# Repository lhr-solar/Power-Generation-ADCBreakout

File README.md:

# PowerGen-ADCBreakout  

Mouser Cart: https://www.mouser.com/Tools/Project/Share?AccessID=0415efee36

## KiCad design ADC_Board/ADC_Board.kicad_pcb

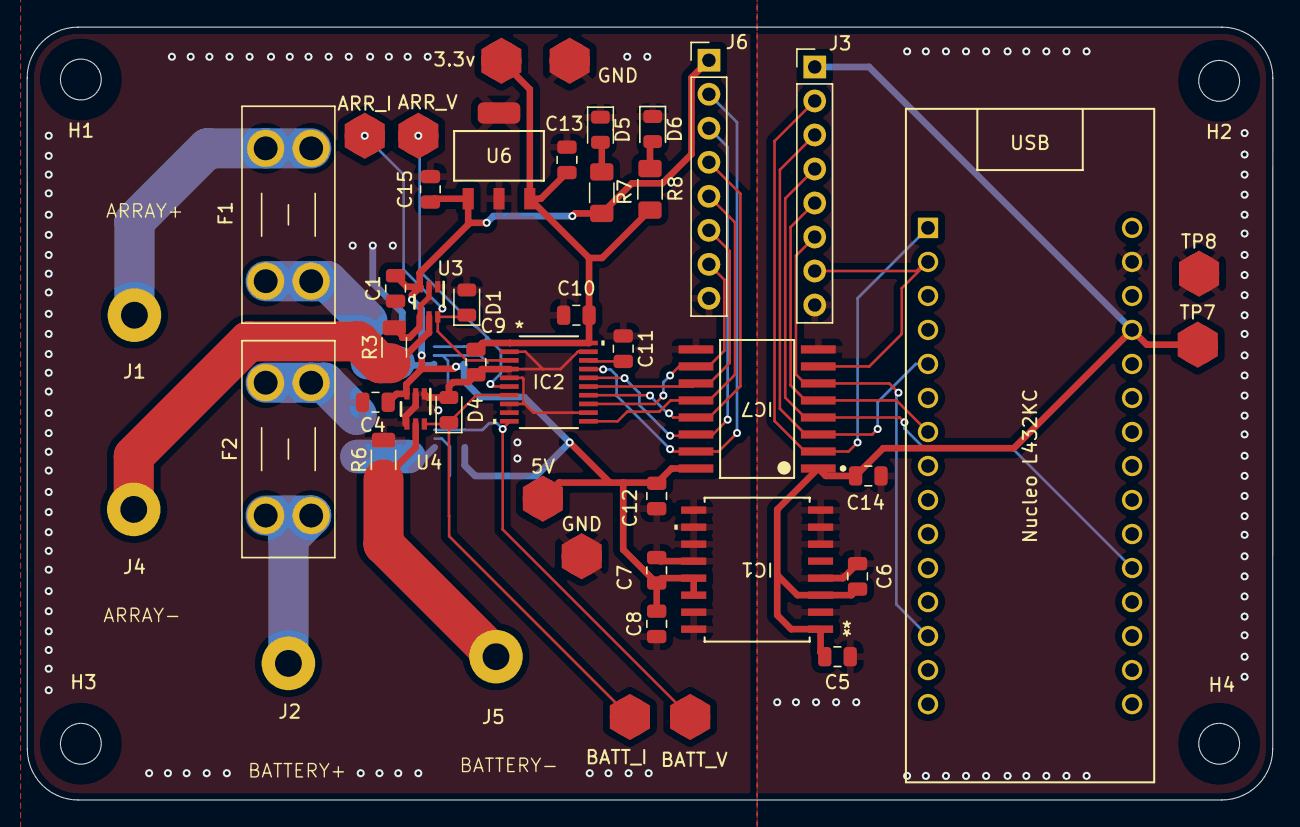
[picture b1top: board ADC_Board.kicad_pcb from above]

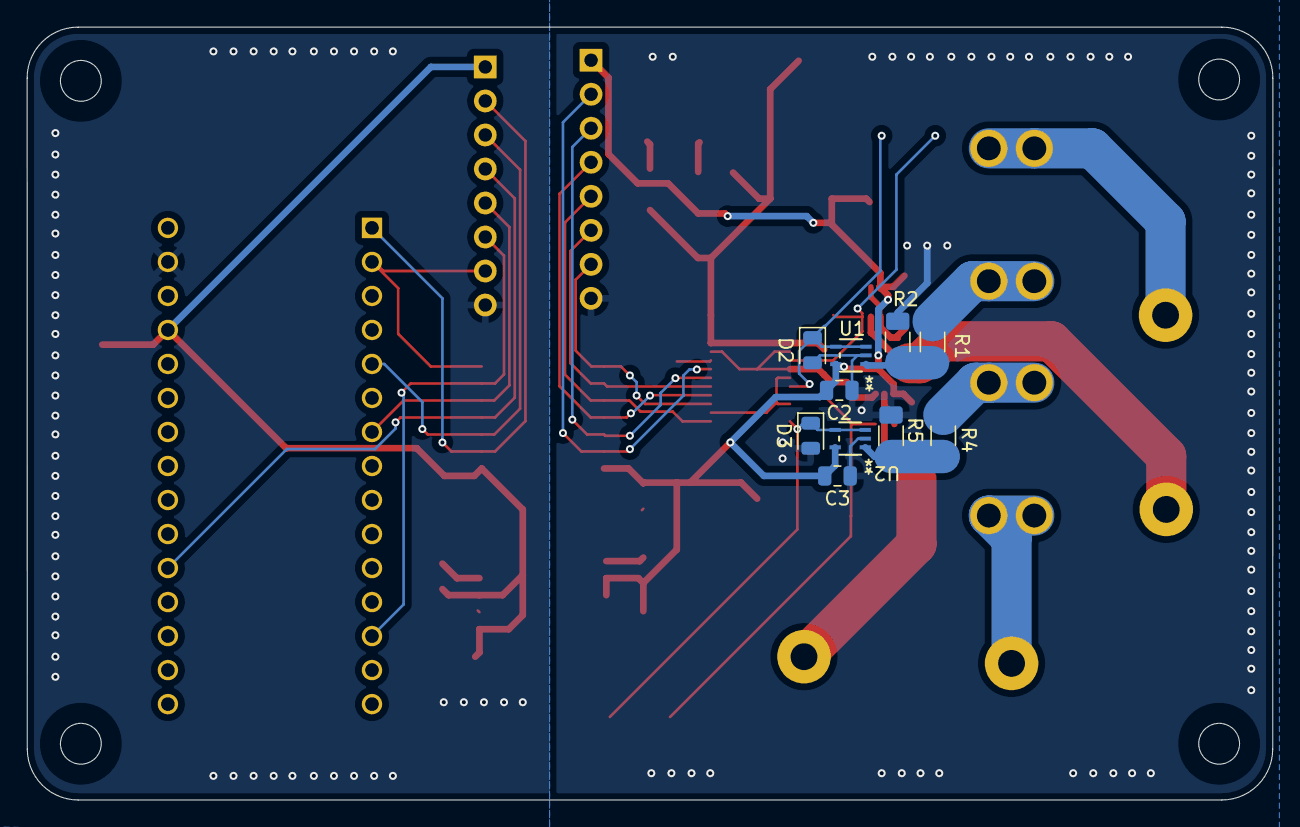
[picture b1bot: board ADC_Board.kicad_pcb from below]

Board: 2 copper layers, 93.0 x 57.7 mm, 60 parts (10 on the bottom side), 32 nets.

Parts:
3.3v, 5V: TestPoint; TestPoint_HEX_3mmID
ARR_I: ARRI_TP; TestPoint_HEX_3mmID
ARR_V: ARRV_TP; TestPoint_HEX_3mmID
BATT_I: BATTI_TP; TestPoint_HEX_3mmID
BATT_V: BATTV_TP; TestPoint_HEX_3mmID
C1, C2, C3, C4: 100nF; C_0805_2012Metric
C5, C8, C12, C14: 0.1u; C_0805_2012Metric
C6, C7: 10u; C_0805_2012Metric
C9, C10: 1u; C_0805_2012Metric
C11: 220n; C_0805_2012Metric
C13: 33u; C_0805_2012Metric
C15: 0.47u; C_0805_2012Metric
D1, D4: 3.3V Zener; D_0805_2012Metric
D2, D3: 3V3; D_0805_2012Metric
D5: 5v_LED; LED_0805_2012Metric
D6: 3.3v_LED; LED_0805_2012Metric
F1, F2: Fuse; Fuseholder_Blade_Mini_Keystone_3568
GND: TestPoint; TestPoint_HEX_3mmID
GND#2: TestPoint; TestPoint_HEX_3mmID
H1, H2, H3, H4: MountingHole; MountingHole_4-40_PanHead
IC1: UCC12040DVE; SO_0DVER_TEX
IC2: ADS131M04QPWRQ1; TSSOP20_PW_TEX
IC7: ISO7762FDWR; DW0016B-IPC_A
J1, J2, J4, J5: Conn_01x01_Pin; Banana_Jack_1_Pin_4mm
J3, J6: Conn_01x08_Pin; PinHeader_1x08_P2.54mm_Vertical
R1, R4: 100k; R_1206_3216Metric_Pad1.30x1.75mm_HandSolder
R2, R7: 3k; R_1206_3216Metric_Pad1.30x1.75mm_HandSolder
R3, R6: 2m; R_1206_3216Metric
R5, R8: 2k; R_1206_3216Metric_Pad1.30x1.75mm_HandSolder
TP7, TP8: TestPoint; TestPoint_HEX_3mmID
U1, U2: OPA990IDCKR; SC_90IDCKR_TEX
U3, U4: INA210AIDCKR; DCK0006A_N
U5: Nucleo_L432KC; NucleoL432KC
U6: LM3940IMP-3.3; MP04A

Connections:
+3.3V: 3.3v.1, C9.1, C10.1, C13.1, IC2.1 (AVDD), IC2.20 (DVDD), R8.1, U6.3 (OUT)
+5V: 5V.1, C1.2, C2.2, C3.2, C4.2, C7.2, C8.2, C12.1, C15.1, IC1.13 (SEL), IC1.14 (VISO), IC7.16 (VCC2), J6.1, R7.1, U1.5 (V+), U2.5 (V+), U3.3 (V+), U4.3 (V+), U6.1 (IN)
+5V_I: C5.2, C6.1, C14.1, IC1.1 (EN), IC1.3 (VINP), IC7.1 (VCC1), J3.1, TP7.1, U5.27 (+5V)
/ADC_DRIVER_CLK: IC2.17 (CLKIN), IC7.15 (OUTA), J6.2
/ADC_DRIVER_CLK_I: IC7.2 (INA), J3.2, U5.1 (D1)
/ARR+: F1.1, J1.1
/ARR+_IN: F1.2, R1.2
/ARR-: J4.1, R3.1, U3.5 (IN-)
/ARRAY_CURRENT+: ARR_I.1, D1.1 (K), IC2.3 (AIN0P), U3.6 (OUT)
/ARRAY_VOLTAGE+: ARR_V.1, D2.1 (K), IC2.6 (AIN1P), U1.3 (IN-), U1.4 (OUT)
/BATT+_IN: F2.2, R4.2
/BATTERY+: F2.1, J2.1
/BATTERY-: J5.1, R6.1, U4.5 (IN-)
/BATTERY_CURRENT+: BATT_I.1, D4.1 (K), IC2.7 (AIN2P), U4.6 (OUT)
/BATTERY_VOLTAGE+: BATT_V.1, D3.1 (K), IC2.10 (AIN3P), U2.3 (IN-), U2.4 (OUT)
/DRDY: IC2.13 (~DRDY), IC7.10 (INF), J6.7
/DRDY_I: IC7.7 (OUTF), J3.7, U5.2 (D0)
/MISO: IC2.15 (DOUT), IC7.11 (INE), J6.6
/MISO_I: IC7.6 (OUTE), J3.6, U5.13 (D10)
/MOSI: IC2.16 (DIN), IC7.14 (OUTB), J6.3
/MOSI_I: IC7.3 (INB), J3.3, U5.5 (D2)
/SPI_CLOCK: IC2.14 (SCLK), IC7.13 (OUTC), J6.4
/SPI_CLOCK_I: IC7.4 (INC), J3.4, U5.20 (A1)
/SYNC/RESET: IC2.11 (~SYNC/~RESET), IC7.12 (OUTD), J6.5
/SYNC/RESET_I: IC7.5 (IND), J3.5, U5.7 (D4)
GND: C1.1, C2.1, C3.1, C4.1, C7.1, C8.1, C9.2, C10.2, C11.1, C12.2, C13.2, C15.2, D1.2 (A), D2.2 (A), D3.2 (A), D4.2 (A), D5.1 (K), D6.1 (K), GND.1, GND#2.1, IC1.9 (GNDS_1), IC1.10 (NC_4), IC1.11 (NC_5), IC1.12 (NC_6), IC1.15 (GNDS_2), IC1.16 (GNDS_3), IC2.2 (AGND), IC2.4 (AIN0N), IC2.5 (AIN1N), IC2.8 (AIN2N), IC2.9 (AIN3N), IC2.12 (~CS), IC2.19 (DGND), IC7.9 (GND2), J6.8, R2.2, R3.2, R5.2, R6.2, U1.2 (V-), U2.2 (V-), U3.1 (REF), U3.2 (GND), U3.4 (IN+), U4.1 (REF), U4.2 (GND), U4.4 (IN+), U6.2 (GND), U6.4
GND_I: C5.1, C6.2, C14.2, IC1.2 (GNDP), IC1.4 (SYNC), IC1.6 (NC_1), IC1.7 (NC_2), IC1.8 (NC_3), IC7.8 (GND1), J3.8, TP8.1, U5.29 (GND)
unnamed: D5.2 (A), R7.2
unnamed: D6.2 (A), R8.2
unnamed: C11.2, IC2.18 (CAP)
unnamed: R1.1, R2.1, U1.1 (IN+)
unnamed: R4.1, R5.1, U2.1 (IN+)

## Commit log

2024-11-01 Initial commit of first iteration
2024-11-01 gitignore file to not ensure we don't track changes of irrelevant files
2024-11-01 Schematic with RC filter on Op Amps
2024-11-02 Changes made after v1 to address Lakshay and Ishaans comments
2024-11-02 Added RC filters to first commit of v2 during workday
2024-11-09 add gitignore
2024-11-09 fix gitignore
2024-11-09 fix another gitignore problem
2024-11-09 removed cached
2024-11-09 Addressed the comments from Champeys review. Including adding an isolation chip for the SPI. Changing Amplifiers to non-isolating to avoid running signal through ADC twice. As well as a few small cha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
2024-11-09 Made changes to address Champey's review. Including replacing isolated amplifiers with standard amplifiers and adding a digital isolator to the SPI communication between the ADC and the Nucleo. Also 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
2024-11-23 Fixed some small issues from last review, and resolved all ERC problems
2024-11-23 Addressed small issues from ERC and from review, also updated symbols and made sure all datasheets were linked
2024-11-23 Smalll changes made to address ERC issues and review, also updated symbols and ensured all datasheets were linked
2024-11-23 Small changes made to address ERC and review, also updated symbols and added datasheet links
2024-11-23 added symbols
2024-12-04 Created Layout
2024-12-30 Added 3.3v input power to schematic
2025-01-24 Added a few small things to address reviews. Made a lot of improvements to readability.
2025-02-01 Same schematic as v2.1 with layout reiterated.
2025-03-02 final iteration of schematic before printing
2025-03-02 added gerber files
2025-03-12 made changes to layout and schematic
2025-03-12 Added gerbers
2025-03-25 Addressed Ravi's Review
2025-03-25 Adressed Ravis Review
2025-03-26 Fixed LDO pad, moved bypass caps, added more stitching vias, and cleaned up some silkscreen stuff
2025-03-29 cleaned up some traces
